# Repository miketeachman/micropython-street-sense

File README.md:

# Street Sense

Street Sense is a MicroPython based project to build a portable, battery-powered sensor unit to measure: 

- **Air Quality**
    - Ozone
    - NO2 
    - Particulates 
- **Noise Pollution**
- **Environment**
    - Temperature
    - Humidity

## Detailed project documentation:
[Street Sense Project at Hackaday IO](https://hackaday.io/project/162059-street-sense)

## Dependencies
### Hardware 
Lolin D32 Pro  
<https://wiki.wemos.cc/products:d32:d32_pro>
### Micropython
fork of micropython
https://github.com/miketeachman/micropython/tree/esp32-i2s-streetsense-littlevgl
which includes these customizations:
- I2S module to read audio samples from an I2S microphone. [link](https://github.com/miketeachman/micropython/blob/esp32-i2s-streetsense-littlevgl/ports/esp32/machine_i2s.c)
- dba module for calculating dB(A) from a stream of audio samples. [link](https://github.com/miketeachman/micropython/blob/esp32-i2s-streetsense-littlevgl/ports/esp32/moddba.c)  
- i2stools module for efficient copy/pruning of audio samples. [link](https://github.com/miketeachman/micropython/blob/esp32-i2s-streetsense-littlevgl/ports/esp32/modi2stools.c)
- integration of littlevGL graphics library. [link](https://github.com/miketeachman/lv_binding_micropython/tree/lvgl-streetsense)

### MicroPython Modules

| name|link|
|----    | ----- |
|asyn    | https://github.com/peterhinch/micropython-async/blob/master/asyn.py  |
|aswitch | https://github.com/peterhinch/micropython-async/blob/master/aswitch.py |
|uasyncio (fast\_io) | https://github.com/peterhinch/micropython-async/tree/master/fast_io  |
|ms\_timer| https://github.com/peterhinch/micropython-async/blob/master/fast_io/ms_timer.py      |
|pms5003: | https://github.com/miketeachman/micropython-pms5003-minimal   |   
|urtc:    | https://github.com/adafruit/Adafruit-uRTC      |
|ads1219: | https://github.com/miketeachman/micropython-ads1219|
|si7021:  | https://github.com/chrisbalmer/micropython-si7021|
|mqtt\_as:| https://github.com/kevinkk525/micropython-mqtt/tree/pause_resume|
|logging: | https://github.com/micropython/micropython-lib/tree/master/logging|

### MicroPython Libs
fork of littlevgl graphics library with customizations
https://github.com/miketeachman/lv_binding_micropython/commits/lvgl-streetsense

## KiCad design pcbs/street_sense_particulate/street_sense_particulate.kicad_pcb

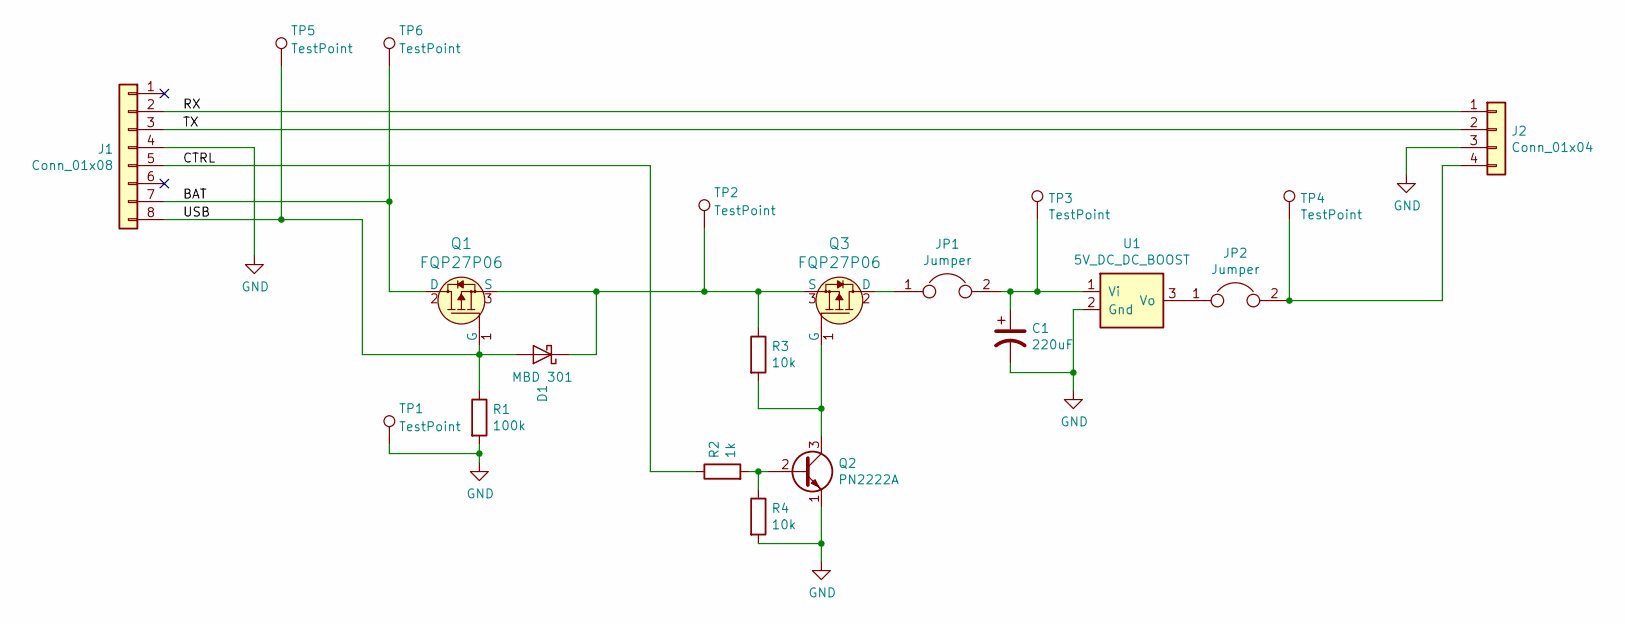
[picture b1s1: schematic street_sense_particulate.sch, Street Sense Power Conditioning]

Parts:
C1: 220uF; CP_Radial_D5.0mm_P2.50mm
D1: MBD 301; D_A-405_P5.08mm_Vertical_AnodeUp
J1: Conn_01x08; PinHeader_1x08_P2.54mm_Vertical
J2: Conn_01x04; PinHeader_1x04_P2.54mm_Vertical
JP1, JP2: Jumper; SolderJumper-2_P1.3mm_Open_Pad1.0x1.5mm
Q1, Q3: FQP27P06; TO-220-3; MPN FQP27P06; Digi-Key_PN FQP27P06-ND
Q2: PN2222A; TO-92-3_Formed_Leads
R1: 100k; R_Axial_DIN0207_L6.3mm_D2.5mm_P10.16mm_Horizontal
R2: 1k; R_Axial_DIN0207_L6.3mm_D2.5mm_P10.16mm_Horizontal
R3: 10k; R_Axial_DIN0309_L9.0mm_D3.2mm_P12.70mm_Horizontal
R4: 10k; R_Axial_DIN0204_L3.6mm_D1.6mm_P2.54mm_Vertical
TP1, TP2, TP3, TP4, TP5, TP6: TestPoint; TestPoint_Loop_D2.50mm_Drill1.0mm
U1: 5V_DC_DC_BOOST; TO-220-3

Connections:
/BAT: J1.7, Q1.2 (D), TP6.1
/CTRL: J1.5, R2.1
/RX: J1.2, J2.1
/TX: J1.3, J2.2
/USB: D1.2 (A), J1.8, Q1.1 (G), R1.1, TP5.1
GND: C1.2, J1.4, J2.3, Q2.1 (E), R1.2, R4.2, TP1.1, U1.2 (Gnd)
unnamed: C1.1, JP1.2, TP3.1, U1.1 (Vi)
unnamed: D1.1 (K), Q1.3 (S), Q3.3 (S), R3.1, TP2.1
unnamed: J2.4, JP2.2, TP4.1
unnamed: JP1.1, Q3.2 (D)
unnamed: JP2.1, U1.3 (Vo)
unnamed: Q2.2 (B), R2.2, R4.1
unnamed: Q2.3 (C), Q3.1 (G), R3.2

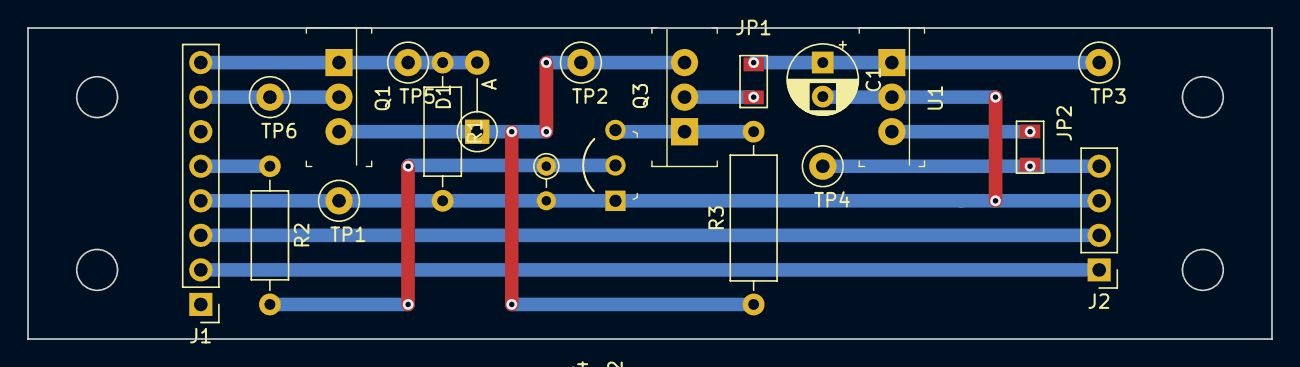
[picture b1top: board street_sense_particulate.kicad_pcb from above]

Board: 2 copper layers, 91.4 x 22.9 mm, 20 parts (0 on the bottom side), 13 nets.

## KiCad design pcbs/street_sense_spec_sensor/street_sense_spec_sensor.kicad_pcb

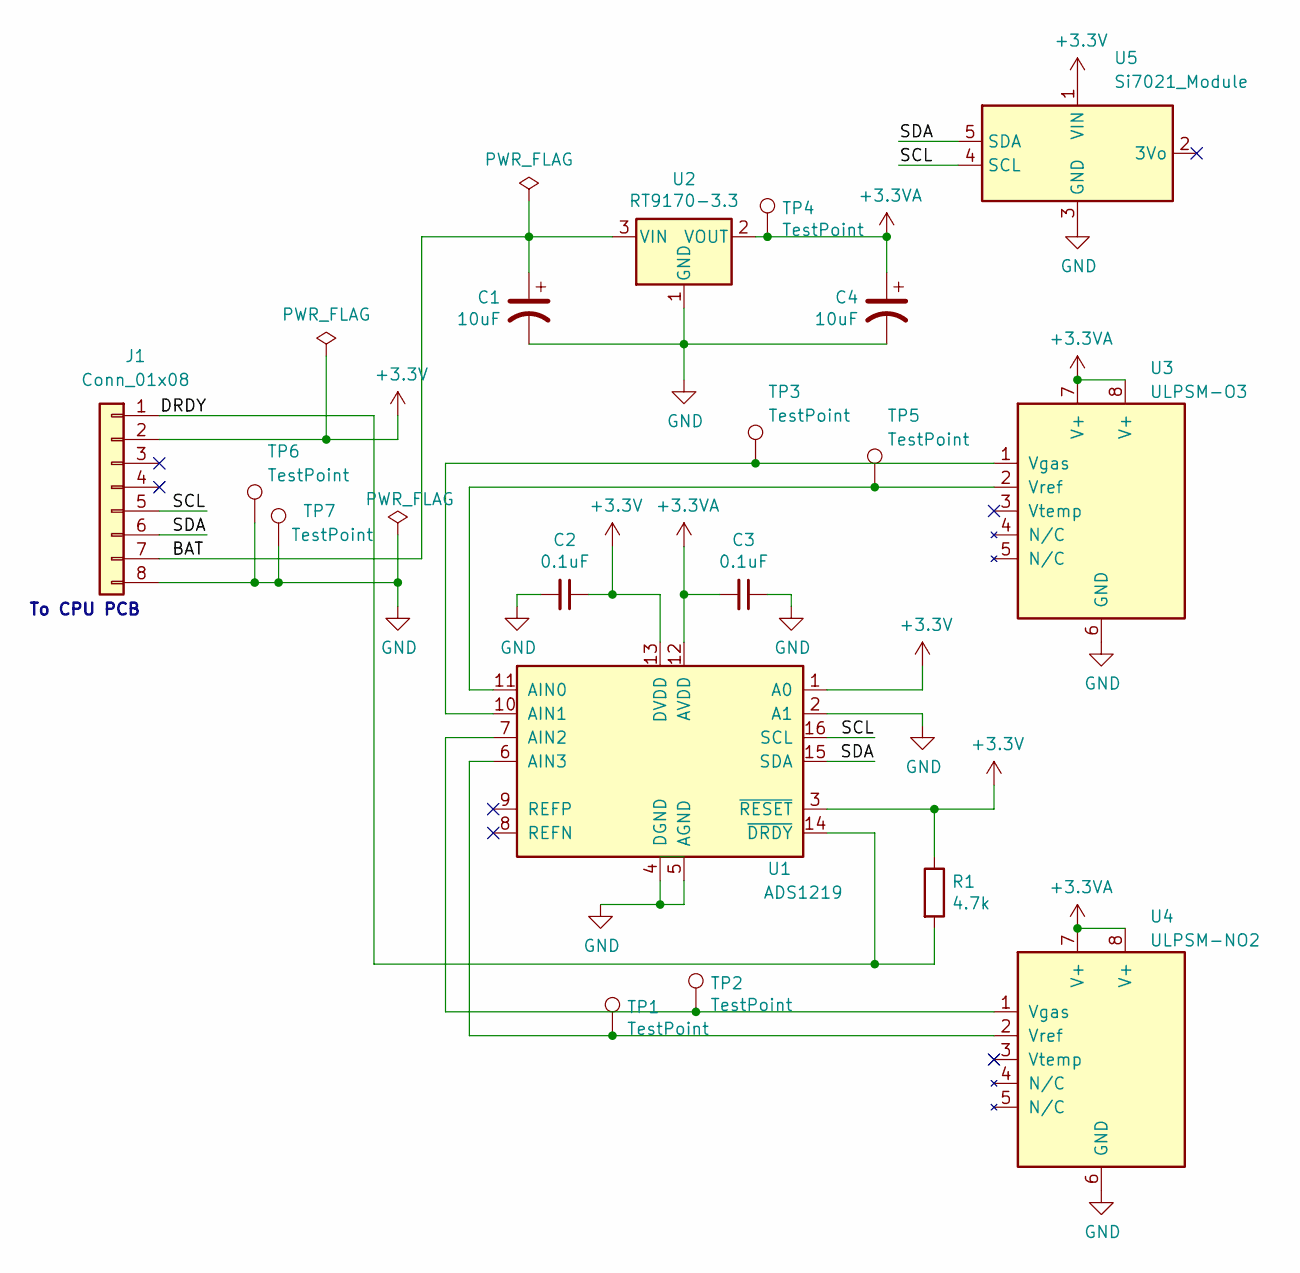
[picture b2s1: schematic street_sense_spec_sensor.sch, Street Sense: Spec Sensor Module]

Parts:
C1: 10uF; CP_Radial_Tantal_D4.5mm_P2.50mm
C2, C3: 0.1uF; C_Disc_D4.3mm_W1.9mm_P5.00mm
C4: 10uF; CP_Radial_Tantal_D4.5mm_P5.00mm
J1: Conn_01x08; connector_8pin
R1: 4.7k; R_Axial_DIN0204_L3.6mm_D1.6mm_P2.54mm_Vertical
TP1, TP2, TP3, TP4, TP5, TP6, TP7: TestPoint; TestPoint_Loop_D2.50mm_Drill1.0mm
U1: ADS1219; ADS1219_Module
U2: RT9170-3.3; RT9170_Module
U3: ULPSM-O3; Spec_Sensor_ULPSM_Module
U4: ULPSM-NO2; Spec_Sensor_ULPSM_Module
U5: Si7021_Module

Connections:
+3.3VA: C3.2, C4.1, TP4.1, U1.12 (AVDD), U2.2 (VOUT), U3.7 (V+), U3.8 (V+), U4.7 (V+), U4.8 (V+)
+3V3: C2.1, J1.2, R1.1, U1.1 (A0), U1.3 (~RESET), U1.13 (DVDD), U5.1 (VIN)
/BAT: C1.1, J1.7, U2.3 (VIN)
/DRDY: J1.1, R1.2, U1.14 (~DRDY)
/SCL: J1.5, U1.16 (SCL), U5.4 (SCL)
/SDA: J1.6, U1.15 (SDA), U5.5 (SDA)
GND: C1.2, C2.2, C3.1, C4.2, J1.8, TP6.1, TP7.1, U1.2 (A1), U1.4 (DGND), U1.5 (AGND), U2.1 (GND), U3.6 (GND), U4.6 (GND), U5.3 (GND)
unnamed: TP1.1, U1.6 (AIN3), U4.2 (Vref)
unnamed: TP2.1, U1.7 (AIN2), U4.1 (Vgas)
unnamed: TP3.1, U1.10 (AIN1), U3.1 (Vgas)
unnamed: TP5.1, U1.11 (AIN0), U3.2 (Vref)

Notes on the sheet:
To CPU PCB

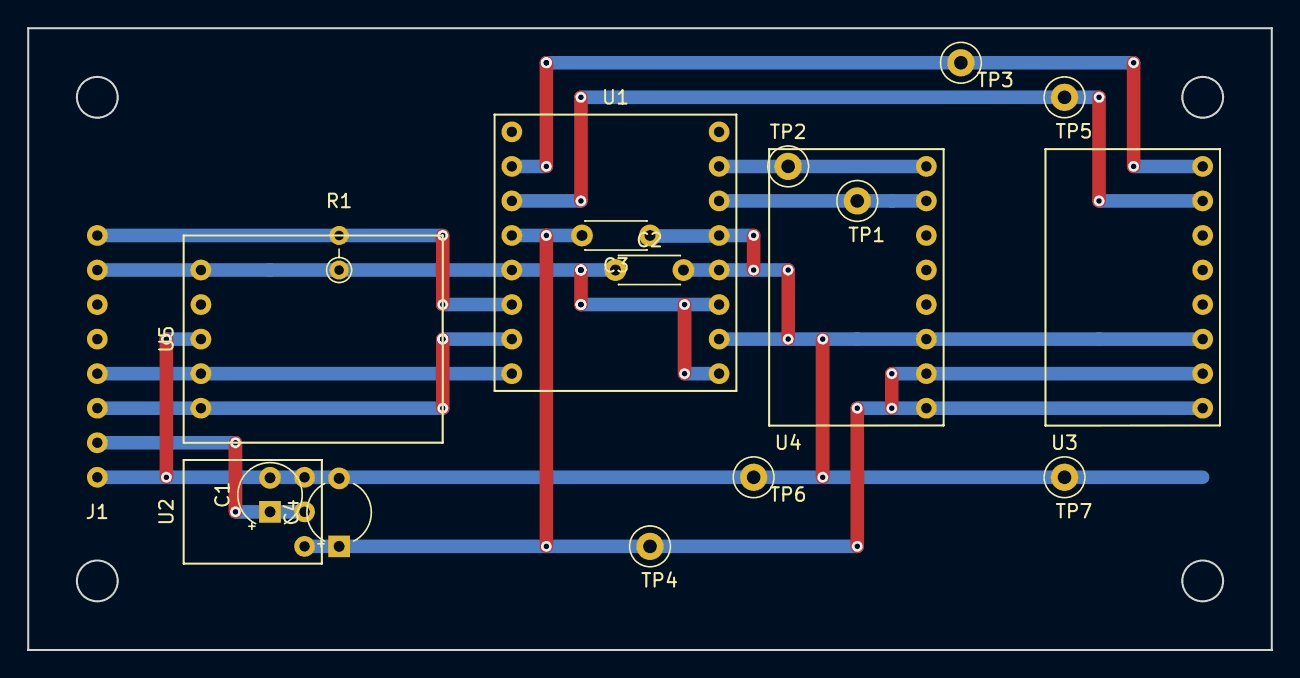
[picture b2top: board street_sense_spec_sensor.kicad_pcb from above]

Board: 2 copper layers, 91.4 x 45.7 mm, 18 parts (0 on the bottom side), 11 nets.

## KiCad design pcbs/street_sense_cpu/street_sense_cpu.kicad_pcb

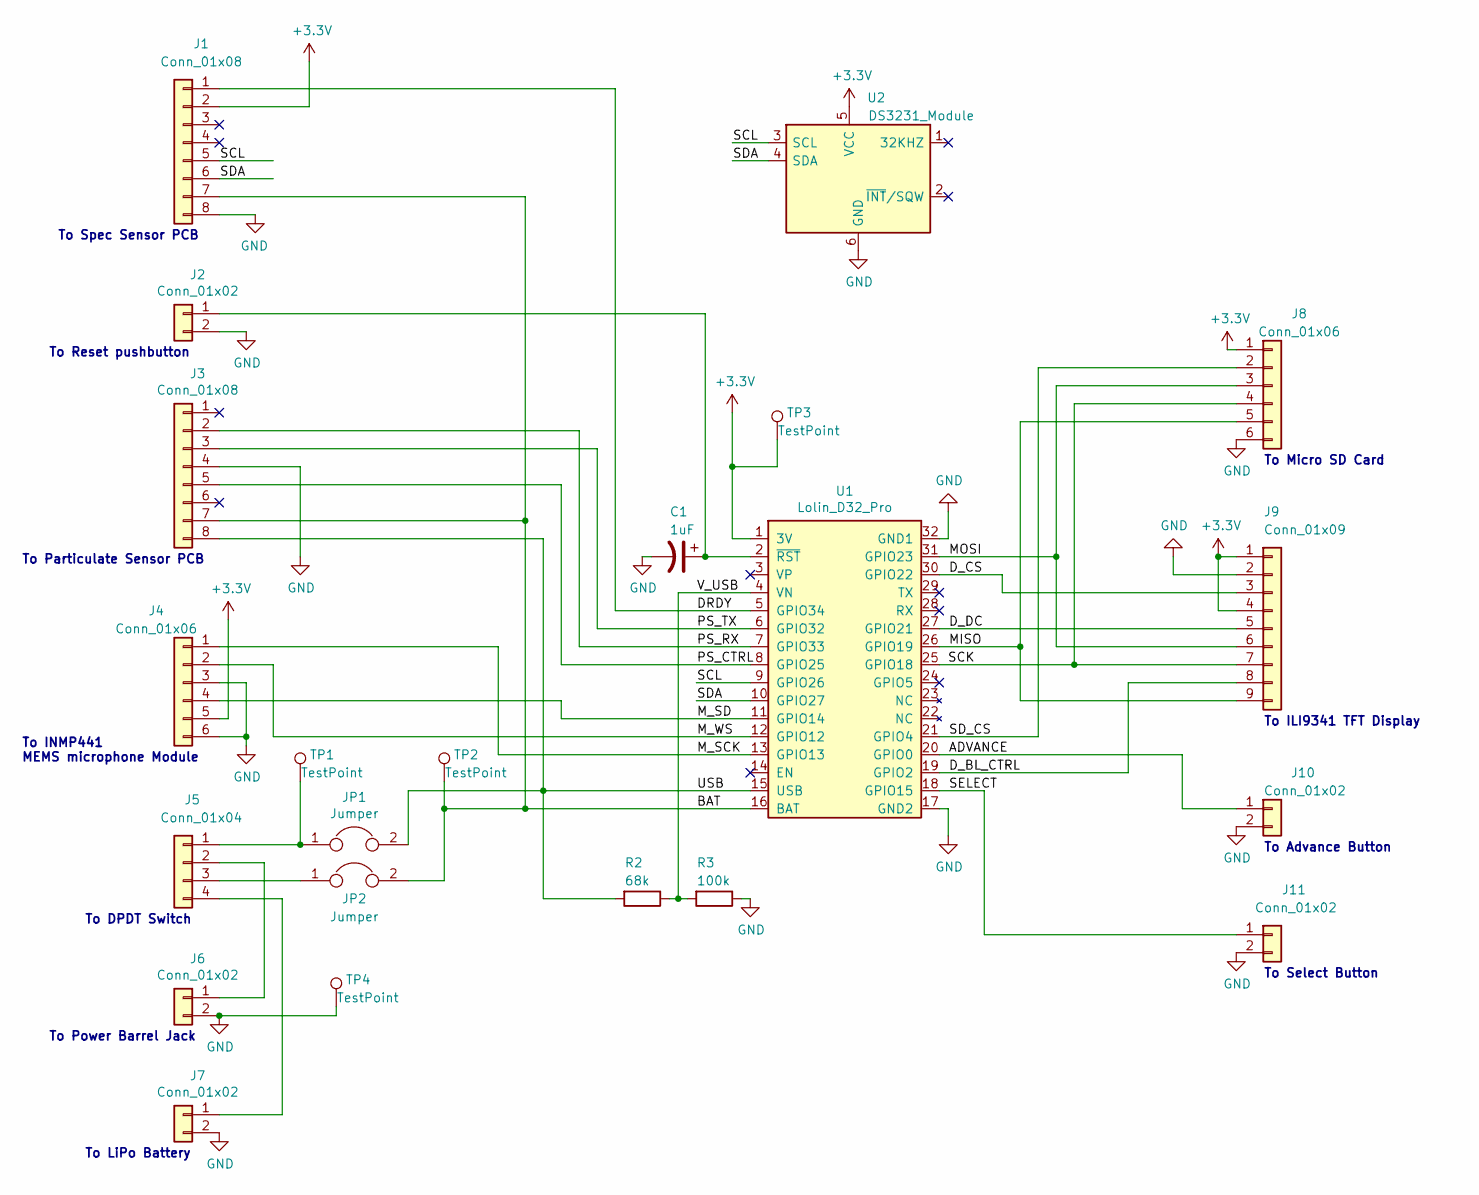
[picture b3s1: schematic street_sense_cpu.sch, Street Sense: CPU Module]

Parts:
C1: 1uF; CP_Radial_D5.0mm_P2.50mm
J1, J3: Conn_01x08; connector_8pin
J2, J6, J7, J10, J11: Conn_01x02; connector_2pin
J4, J8: Conn_01x06; connector_6pin
J5: Conn_01x04; connector_4pin
J9: Conn_01x09; connector_9pin
JP1, JP2: Jumper; SolderJumper-2_P1.3mm_Open_Pad1.0x1.5mm
R2: 68k; R_Axial_DIN0207_L6.3mm_D2.5mm_P7.62mm_Horizontal
R3: 100k; R_Axial_DIN0207_L6.3mm_D2.5mm_P7.62mm_Horizontal
TP1, TP2, TP3, TP4: TestPoint; TestPoint_Loop_D2.50mm_Drill1.0mm
U1: Lolin_D32_Pro; LolinD32
U2: DS3231_Module

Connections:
+3V3: J1.2, J4.5, J8.1, J9.1, J9.4, TP3.1, U1.1 (3V), U2.5 (VCC)
/ADVANCE: J10.1, U1.20 (GPIO0)
/BAT: J1.7, J3.7, JP2.2, TP2.1, U1.16 (BAT)
/DRDY: J1.1, U1.5 (GPIO34)
/D_BL_CTRL: J9.8, U1.19 (GPIO2)
/D_CS: J9.3, U1.30 (GPIO22)
/D_DC: J9.5, U1.27 (GPIO21)
/MISO: J8.5, J9.9, U1.26 (GPIO19)
/MOSI: J8.3, J9.6, U1.31 (GPIO23)
/M_SCK: J4.1, U1.13 (GPIO13)
/M_SD: J4.4, U1.11 (GPIO14)
/M_WS: J4.2, U1.12 (GPIO12)
/PS_CTRL: J3.5, U1.8 (GPIO25)
/PS_RX: J3.2, U1.7 (GPIO33)
/PS_TX: J3.3, U1.6 (GPIO32)
/SCK: J8.4, J9.7, U1.25 (GPIO18)
/SCL: J1.5, U1.9 (GPIO26), U2.3 (SCL)
/SDA: J1.6, U1.10 (GPIO27), U2.4 (SDA)
/SD_CS: J8.2, U1.21 (GPIO4)
/SELECT: J11.1, U1.18 (GPIO15)
/USB: J3.8, JP1.2, R2.2, U1.15 (USB)
/V_USB: R2.1, R3.2, U1.4 (VN)
GND: C1.2, J1.8, J2.2, J3.4, J4.3, J4.6, J6.2, J7.2, J8.6, J9.2, J10.2, J11.2, R3.1, TP4.1, U1.17 (GND2), U1.32 (GND1), U2.6 (GND)
unnamed: C1.1, J2.1, U1.2 (~RST)
unnamed: J5.1, JP1.1, TP1.1
unnamed: J5.2, J6.1
unnamed: J5.3, JP2.1
unnamed: J5.4, J7.1

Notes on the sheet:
To INMP441 MEMS microphone Module
To Particulate Sensor PCB
To Reset pushbutton
To LiPo Battery
To Power Barrel Jack
To Micro SD Card
To ILI9341 TFT Display
To Advance Button
To Select Button
To Spec Sensor PCB
To DPDT Switch

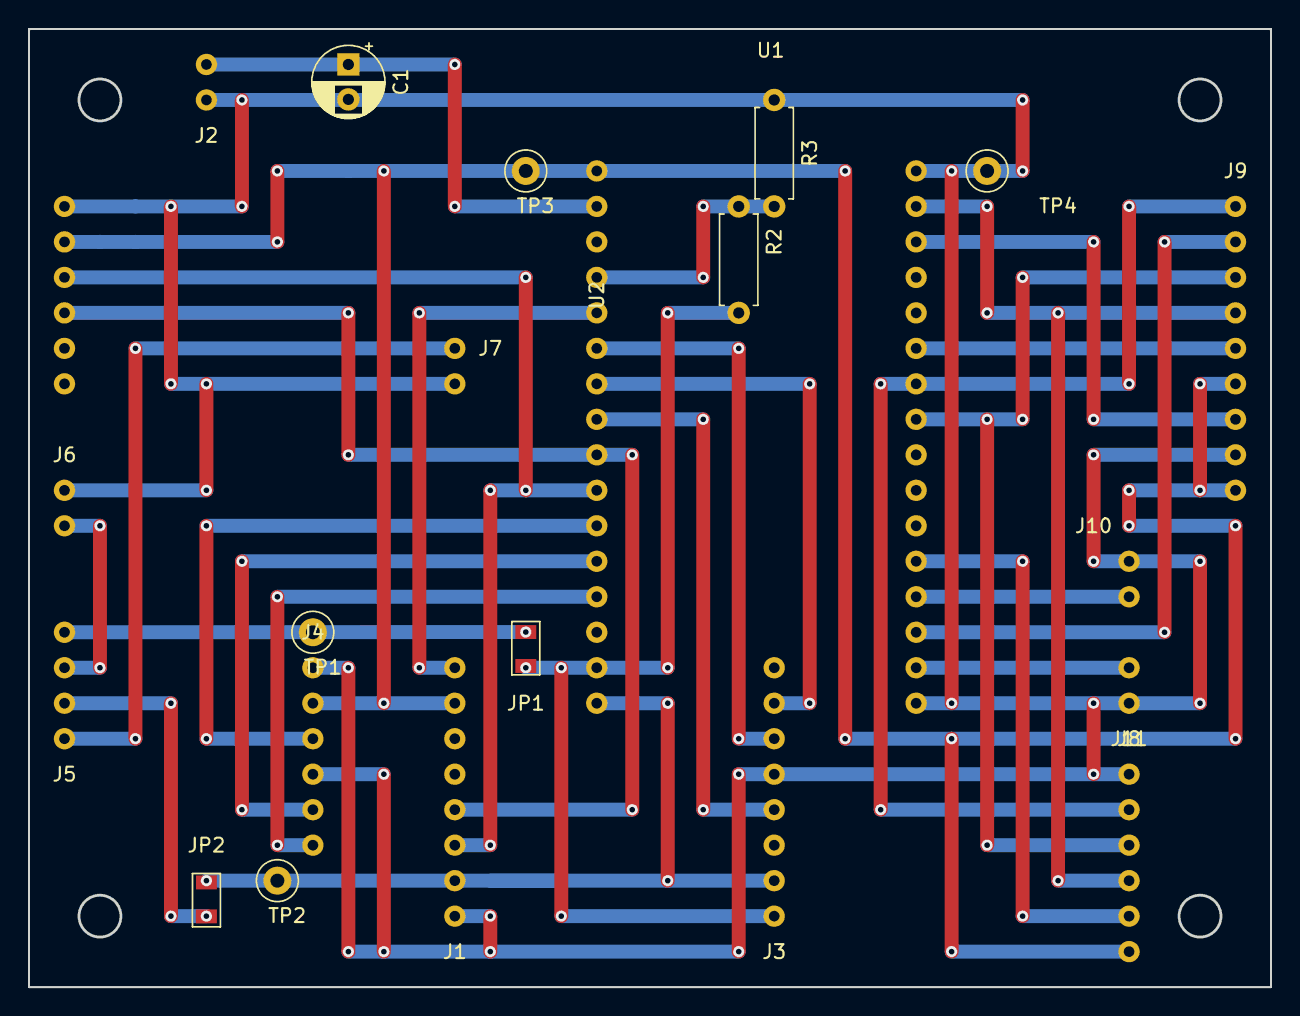
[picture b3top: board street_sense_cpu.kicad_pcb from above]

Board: 2 copper layers, 88.9 x 68.5 mm, 22 parts (0 on the bottom side), 28 nets.

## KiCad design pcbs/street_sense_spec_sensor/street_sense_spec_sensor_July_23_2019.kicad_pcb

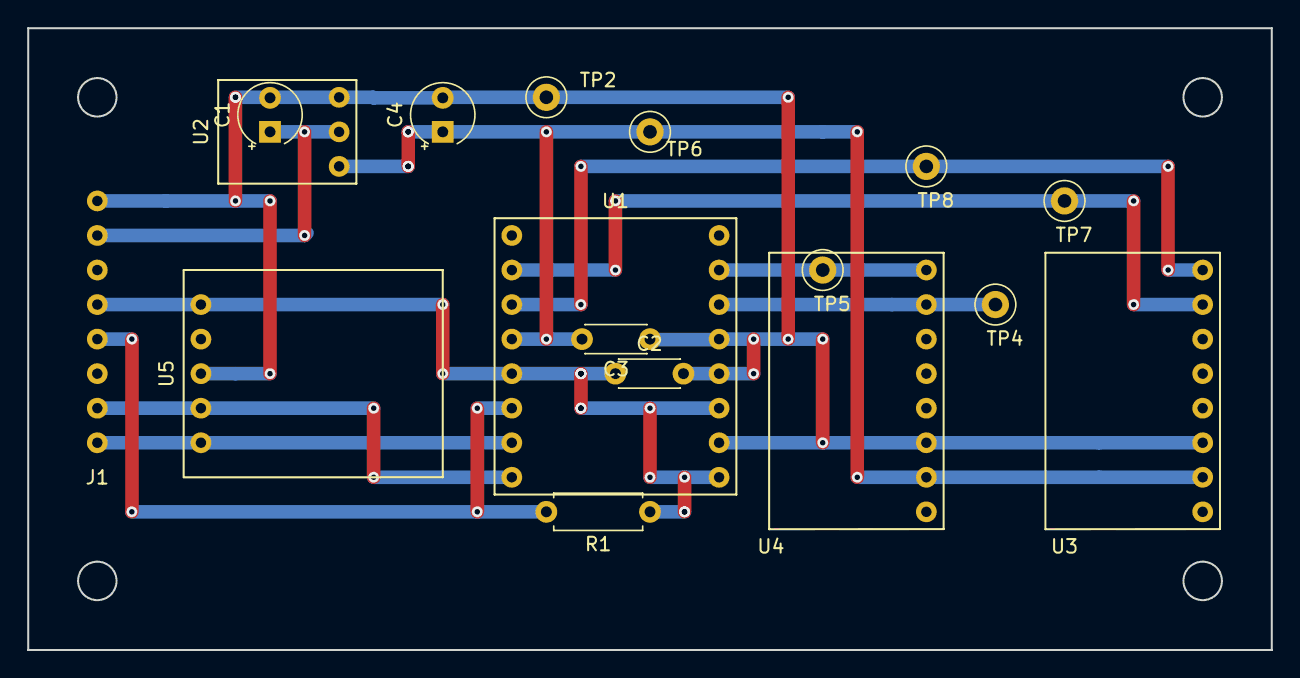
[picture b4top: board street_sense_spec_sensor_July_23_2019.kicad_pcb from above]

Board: 2 copper layers, 91.4 x 45.7 mm, 17 parts (0 on the bottom side), 11 nets.

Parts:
C1, C4: 10uF; CP_Radial_Tantal_D4.5mm_P2.50mm
C2, C3: 0.1uF; C_Disc_D4.3mm_W1.9mm_P5.00mm
J1: Conn_01x08; connector_8pin
R1: 4.7k; R_Axial_DIN0207_L6.3mm_D2.5mm_P7.62mm_Horizontal
TP2, TP4, TP5, TP6, TP7, TP8: TestPoint; TestPoint_Loop_D2.50mm_Drill1.0mm
U1: ADS1219; ADS1219_Module
U2: RT9170-3.3; RT9170_Module
U3: ULPSM-O3; Spec_Sensor_ULPSM_Module
U4: ULPSM-NO2; Spec_Sensor_ULPSM_Module
U5: Si7021_Module

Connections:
+3.3VA: C3.2, C4.1, TP6.1, U1.12, U2.2, U3.7, U4.7
+3V3: C2.1, J1.4, R1.1, U1.1, U1.3, U1.13, U5.1
/BAT: C1.1, J1.2, U2.3
/DRDY: J1.5, R1.2, U1.14
/SCL: J1.7, U1.16, U5.4
/SDA: J1.8, U1.15, U5.5
GND: C1.2, C2.2, C3.1, C4.2, J1.1, TP2.1, U1.2, U1.4, U1.5, U2.1, U3.6, U4.6, U5.3
unnamed: TP4.1, U1.6, U4.2
unnamed: TP5.1, U1.7, U4.1
unnamed: TP7.1, U1.10, U3.2
unnamed: TP8.1, U1.11, U3.1

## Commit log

2018-12-03 First commit of Street Sense project
2018-12-03 added README
2018-12-04 Added support for I2S Microphone
    - read a audio sample block from microphone using I2S protocol
    - prune unused data from sample block
    - write samples to WAV file on SD Card
2018-12-18 added I2C device for ozone, no2 sensors
2018-12-18 removed some debug code
2018-12-27 move microphone coroutine to high priority I/O asyncio queue
2018-12-28 formatting fixes
2019-02-08 integration with new version of I2S class
2019-02-08 adding git files
2019-02-08 first version of schematic
2019-02-08 Updated Schematic
    added the following components:
    - Ozone sensor
    - NO2 sensor
    - OLED 128x64 display
    - ADS1015 12-bit ADC
    - DS3231 RTC
2019-02-12 added pulldown resistor to I2S microphone
    100k ohm pulldown from DOUT to GND
    as described in manufacturer's datasheet
2019-03-15 updated schematic
    added components to reduce power supply rail noise
    created by DC-DC boost converter
2019-03-18 integrated ADS1219 ADC into design (code + schematic)
2019-03-20 updated uPy code and schematic V06 with new I2S microphone
    Replaced Adafruit SPH0645LM4H I2S microphone with INMP441 I2S microphone
2019-03-22 read particulate sensor with Passive mode
2019-03-25 added si7021 temperature/humidity sensor
    - updated uPy code
    - added new symbol to KiCad symbol library
    - updated schematic, v07
2019-03-29 publish sensor data to Adafruit IO using Async MQTT
2019-04-06 Publish sensor data with MQTT-AS and improved microphone sample handling
    - new uasyncio task to publish sensor data to Adafruit IO
    - WiFi and MQTT connect ids and passwords stored in a file
    - microphone sampling loop now yields to uasyncio scheduler when DMA memory does
    not contain a complete block of samples.
2019-05-14 Incremental improvements to measurement performance of O3 and NO2 sensors
    Hardware schematic changes:
    - separate 3.3V analog supply for O3, NO2, and ADC components
    - ~DRDY signal to ESP32 GPIO34
    MicroPython changes:
    - ~DRDY signal used with interrupt to read ADC values (replaces I2C polling)
    - average of 100 samples used to calculate Vref and Vgas measurements
2019-06-26 changed to TFT colour display
    - ILI9340 2.2" 240x360
    - asyncio enabled button to switch display screens
2019-08-01 new schematics for CPU and Spec Sensor Modules
    single schematic split into separate CPU and Spec Sensor Modules
    remapping of GPIO pins in MicroPython code to align with the CPU schematic
2019-09-09 updated CPU schematic
2019-09-13 added PCB design for power conditioning module
2019-09-28 first step to move to mainline from Lobo port
2019-10-26 migration to uPy mainline, littlevGL integration
2019-10-28 added voltage monitor for USB and Lipo battery
2019-11-13 continuous calculation of dbA, every second
    show dBA on display, publish using MQTT, log to SD Card
2019-11-15 added display for dBA measurement
2019-11-15 changed debugging to use logging module from micropython-lib
2019-11-15 WAV header code to separate file
2019-11-16 added first version of global measurement repo
2019-11-17 improvements to SD Card logging
    - timestamps referenced to unix epoch
    - filenames include date/time
    - added o3 and no2 measurements
2019-11-17 updated readme, workaround for sdcard mount() exception
2019-11-17 add header to measurement file, implement display timeout
2019-11-18 optimized handling of ADC interrupts
2019-11-21 added github links for extensions to micropython build
2019-11-22 fixed bug in calcuation of interval time boundary
2019-11-22 added periodic GC
2019-11-27 added new stats to measurement repo, expanded SDCard logging
2019-11-30 fixed 2 bugs: clear vusb stats, log dba max not min
2019-12-06 added bling to dBA screen - screen color changes with dBA reading
2019-12-08 improved backlight control on startup, show reset cause
2019-12-09 added Demo mode
2019-12-12 added global exception catcher
2020-02-21 display buffer optimization, readme correction

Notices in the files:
pcbs/street_sense_cpu/street_sense_cpu.sch:
License:  MIT License (MIT)
